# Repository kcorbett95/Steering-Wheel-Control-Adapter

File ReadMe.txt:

This project is meant to adapt steering wheel media control buttons to aftermarket stereo head-units. It requires the head-unit to use an analog remote
input, usually in the form of a 3.5mm headphone jack in the back of the unit, and the vehicle steering wheel buttons to be a resistor-network type where
each button corresponds to a different resistance value between two wires. Vehicles with many buttons often have 2 input wires and a 3rd reference wire,
where the resistances can be between the reference wire and either input wire, doubling the number of input buttons for the same resistances.

The existing code is currently working on a 2015 Subaru Crosstrek/Impreza and a Pioneer AVH4500NEX head unit. You will need to consult the vehicle
factory service manual to determine what the resistance values for each steering wheel button is, or do some testing with a multimeter to measure each
button manually (this takes forever, don't do this unless you have no other option.) You will also need to know the remote input values the head unit
needs for each function. This information is kindof difficult to find, but I found the values for Pioneer head units after a few hours of digging through
forums and such. An email to the support of your head-unit manufacturer might be helpful in finding this information.

************   MAPPING FUNCITONS    **************
Once you have the required resistance values for both your vehicle, and the corresponding head unit values, the mapping procedure is fairly easy:

1) In the beginning of the SWC_adapter.ino arduino file, you will find the definitions for the head unit values. You will need to replace these values
with the ones for your head unit. 

For example, if your volume up function needs a 55kOhm input, replace the value: 

#define volUp 55000

Repeat this process for the rest of the defined functions. If your vehicle does not have a button corresponding to one of these values, you can either
replace the value with "noBtn" without the quotes if you do not wish to use this function, or you can make a custom value for a button-hold to implement
a different function in later steps (more advanced).

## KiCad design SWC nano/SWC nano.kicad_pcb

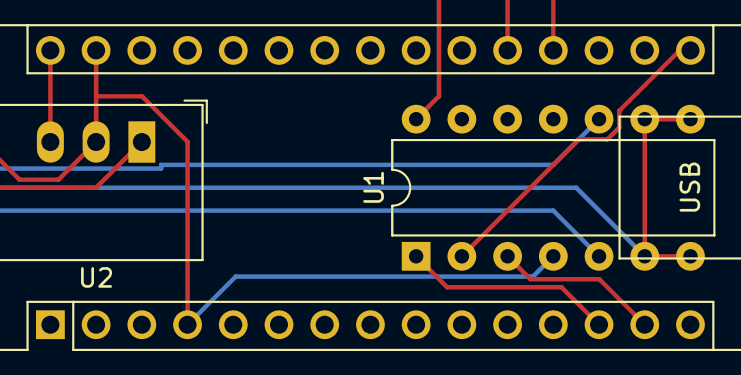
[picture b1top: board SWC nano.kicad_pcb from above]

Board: 2 copper layers, 3 parts (0 on the bottom side), 6 nets.

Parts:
A1: Arduino_Nano_v3.x; Arduino_Nano
U1: MCP4251-xxxx-P; DIP-14_W7.62mm
U2: R-785.0-0.5; Converter_DCDC_RECOM_R-78E-0.5_THT

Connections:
/Remote_Ref: U1.6 (P1W), U1.7 (P1A), U1.8 (P0A), U1.9 (P0W)
/SW_Pos_2: A1.27 (+5V), A1.30 (VIN), U1.14 (VDD), U2.3 (OUT)
GND: A1.4 (GND), A1.29 (GND), U1.4 (VSS), U2.2 (GND)
unnamed: A1.13 (D10), U1.1 (~CS)
unnamed: A1.14 (D11), U1.3 (SDI)
unnamed: A1.16 (D13), U1.2 (SCK)

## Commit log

2023-11-13 Completed code, readme in progress, PCB in progress
2023-12-20 Test code with some adjustments
2026-01-28 NEC command based working
